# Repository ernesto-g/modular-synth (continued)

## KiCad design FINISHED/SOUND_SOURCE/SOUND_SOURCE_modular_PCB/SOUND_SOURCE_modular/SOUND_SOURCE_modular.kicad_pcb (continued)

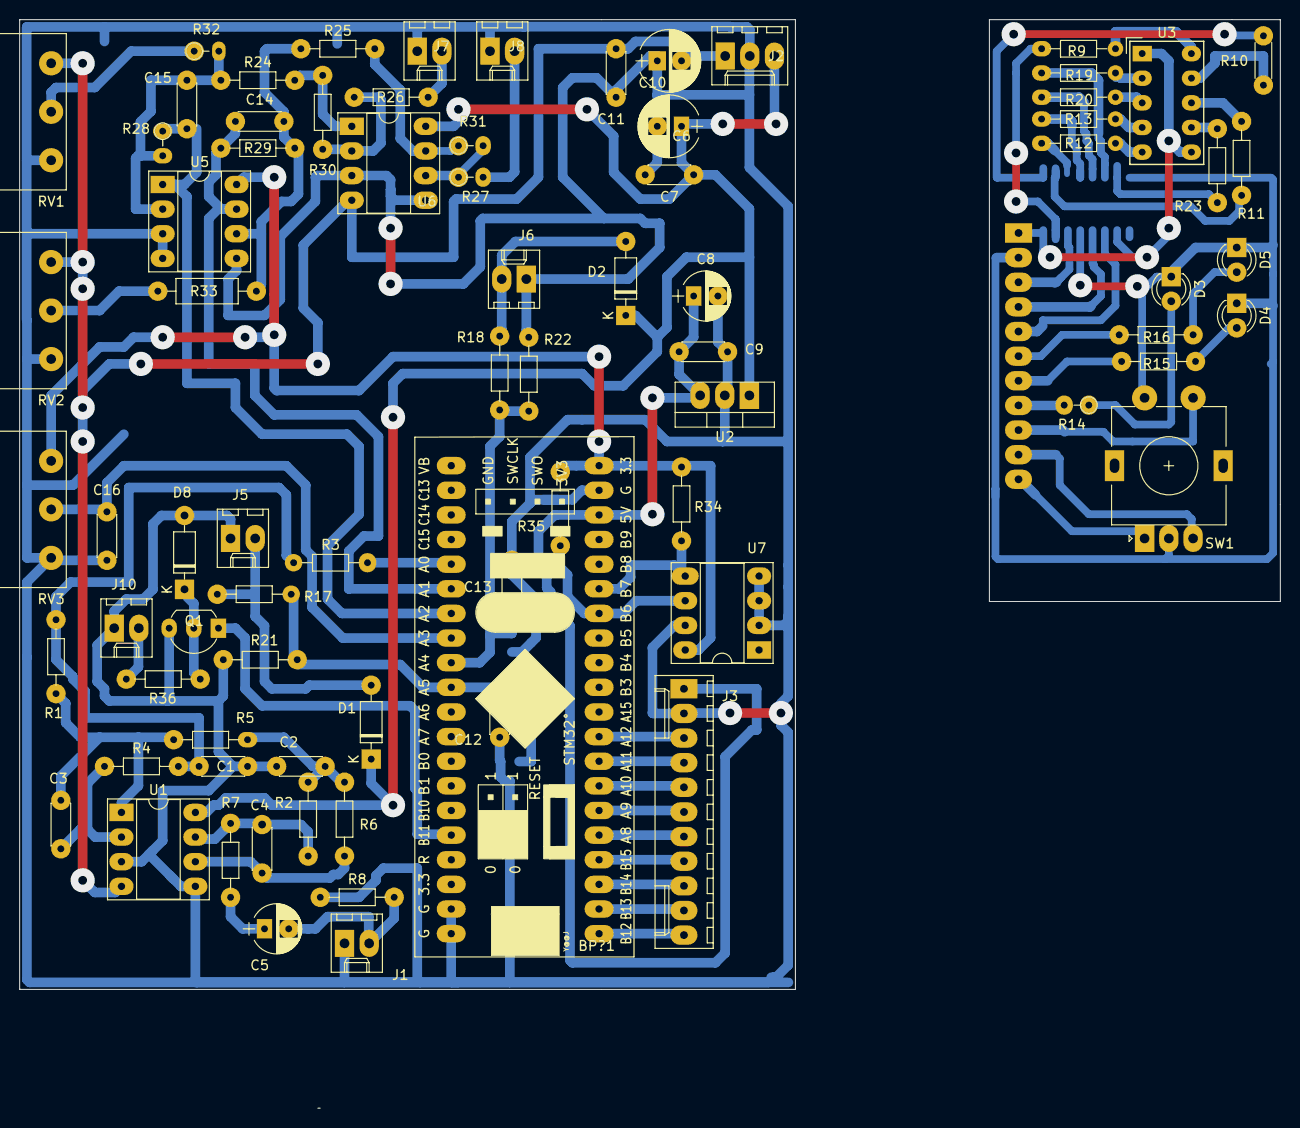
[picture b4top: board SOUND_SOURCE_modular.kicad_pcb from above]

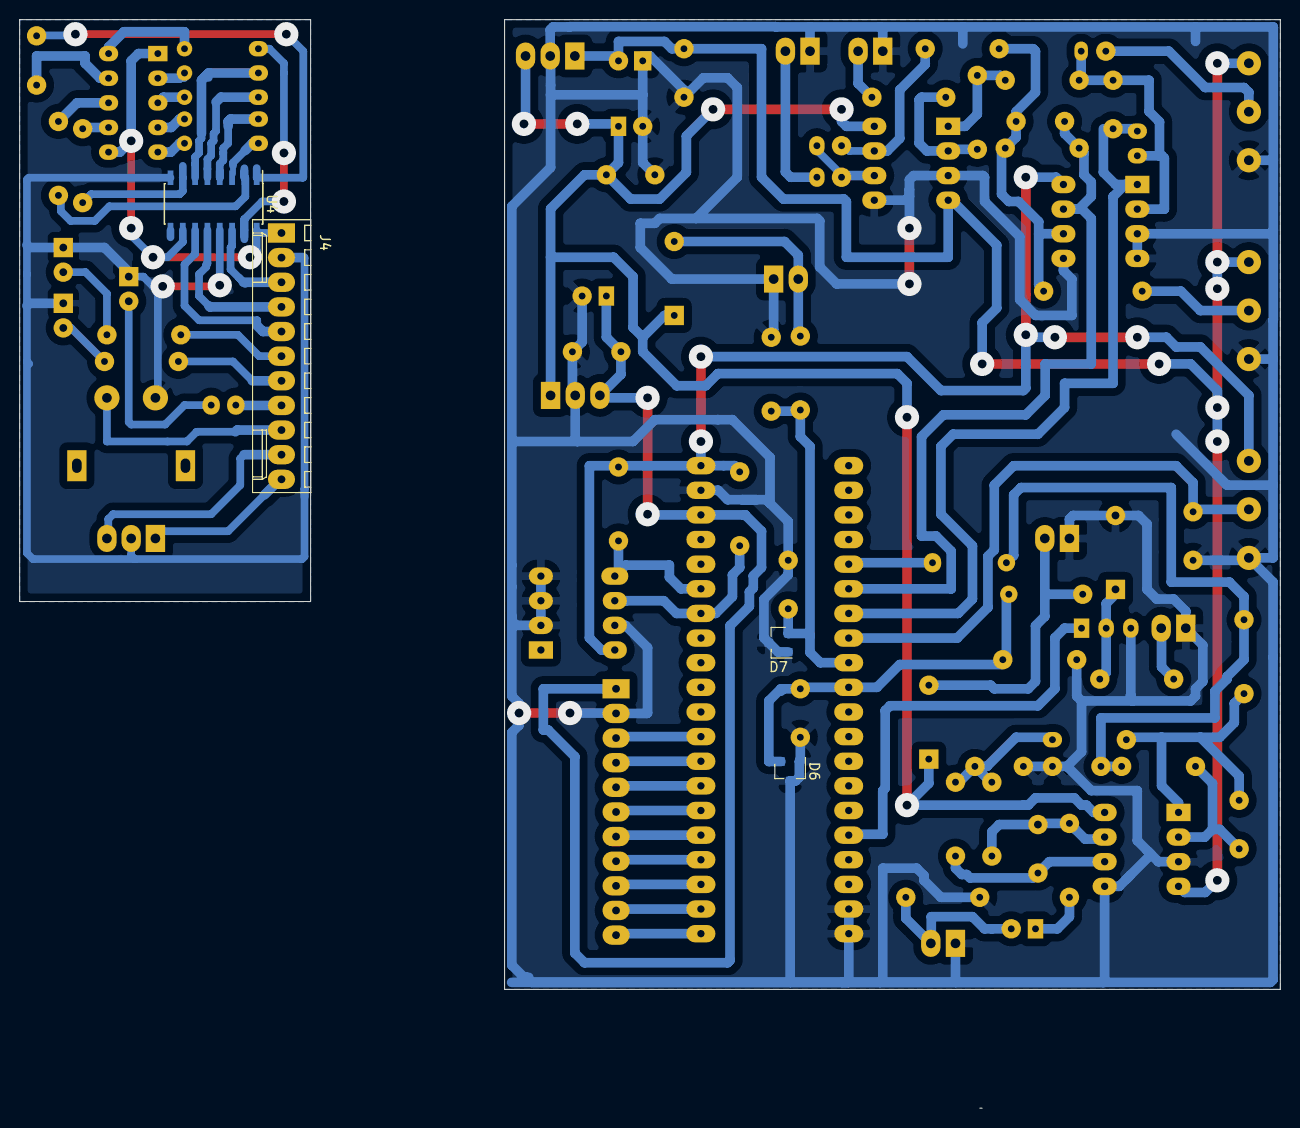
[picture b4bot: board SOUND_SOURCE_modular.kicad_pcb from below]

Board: 2 copper layers, 130.0 x 112.2 mm, 82 parts (4 on the bottom side), 75 nets.

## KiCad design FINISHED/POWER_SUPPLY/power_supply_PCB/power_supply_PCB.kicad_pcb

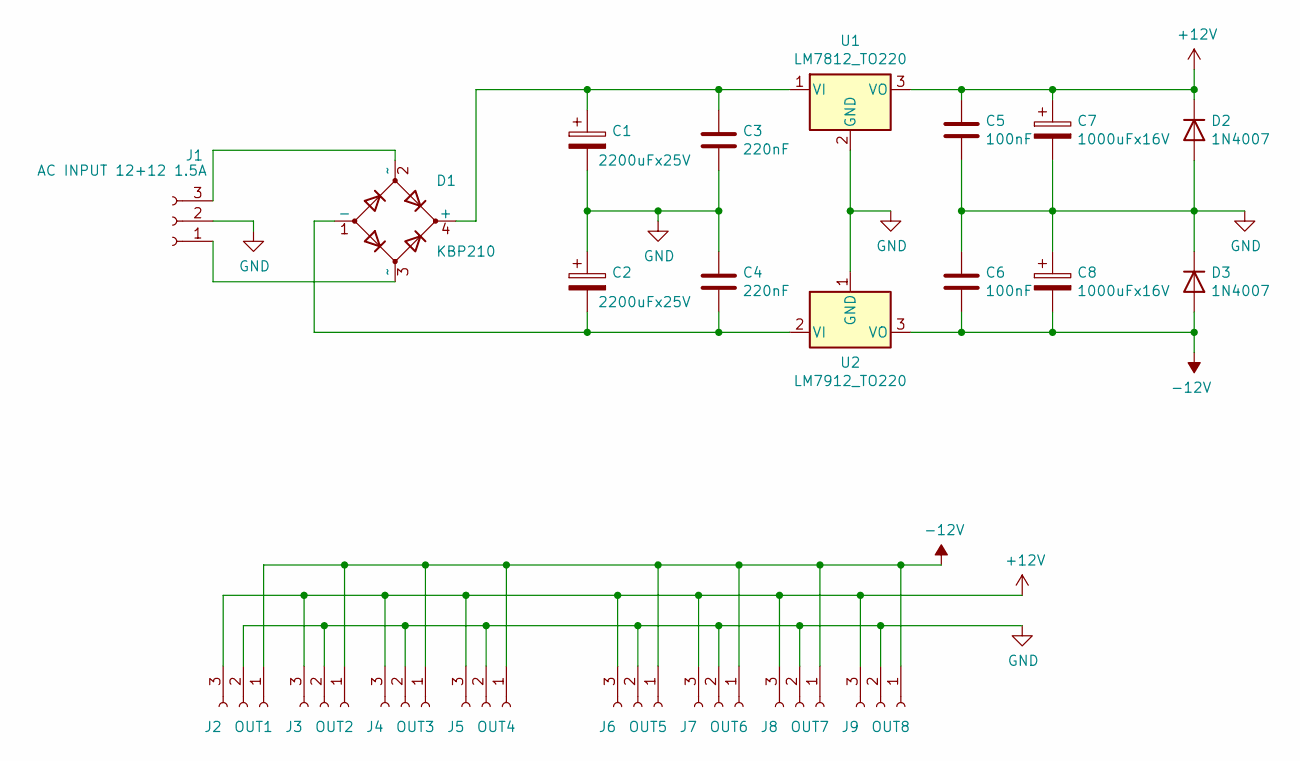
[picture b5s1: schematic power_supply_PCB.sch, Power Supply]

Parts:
C1, C2: 2200uFx25V; CP_Radial_D13.0mm_P5.00mm
C3, C4: 220nF; C_Disc_D11.0mm_W5.0mm_P7.50mm
C5, C6: 100nF; C_Disc_D5.0mm_W2.5mm_P5.00mm
C7, C8: 1000uFx16V; CP_Radial_D8.0mm_P3.50mm
D1: KBP210; Diode_Bridge_Vishay_KBU
D2, D3: 1N4007; D_DO-41_SOD81_P10.16mm_Horizontal
J1: AC INPUT 12+12 1.5A; TerminalBlock_Altech_AK300-3_P5.00mm
J2: OUT1; Molex_KK-6410-03_03x2.54mm_Straight
J3: OUT2; Molex_KK-6410-03_03x2.54mm_Straight
J4: OUT3; Molex_KK-6410-03_03x2.54mm_Straight
J5: OUT4; Molex_KK-6410-03_03x2.54mm_Straight
J6: OUT5; Molex_KK-6410-03_03x2.54mm_Straight
J7: OUT6; Molex_KK-6410-03_03x2.54mm_Straight
J8: OUT7; Molex_KK-6410-03_03x2.54mm_Straight
J9: OUT8; Molex_KK-6410-03_03x2.54mm_Straight
U1: LM7812_TO220; TO-220-3_Vertical
U2: LM7912_TO220; TO-220-3_Vertical

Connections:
+12V: C5.1, C7.1, D2.1 (K), J2.3, J3.3, J4.3, J5.3, J6.3, J7.3, J8.3, J9.3, U1.3 (VO)
-12V: C6.2, C8.2, D3.2 (A), J2.1, J3.1, J4.1, J5.1, J6.1, J7.1, J8.1, J9.1, U2.3 (VO)
GND: C1.2, C2.1, C3.2, C4.1, C5.2, C6.1, C7.2, C8.1, D2.2 (A), D3.1 (K), J1.2, J2.2, J3.2, J4.2, J5.2, J6.2, J7.2, J8.2, J9.2, U1.2 (GND), U2.1 (GND)
unnamed: C1.1, C3.1, D1.4 (+), U1.1 (VI)
unnamed: C2.2, C4.2, D1.1 (-), U2.2 (VI)
unnamed: D1.2 (~~), J1.3
unnamed: D1.3 (~~), J1.1

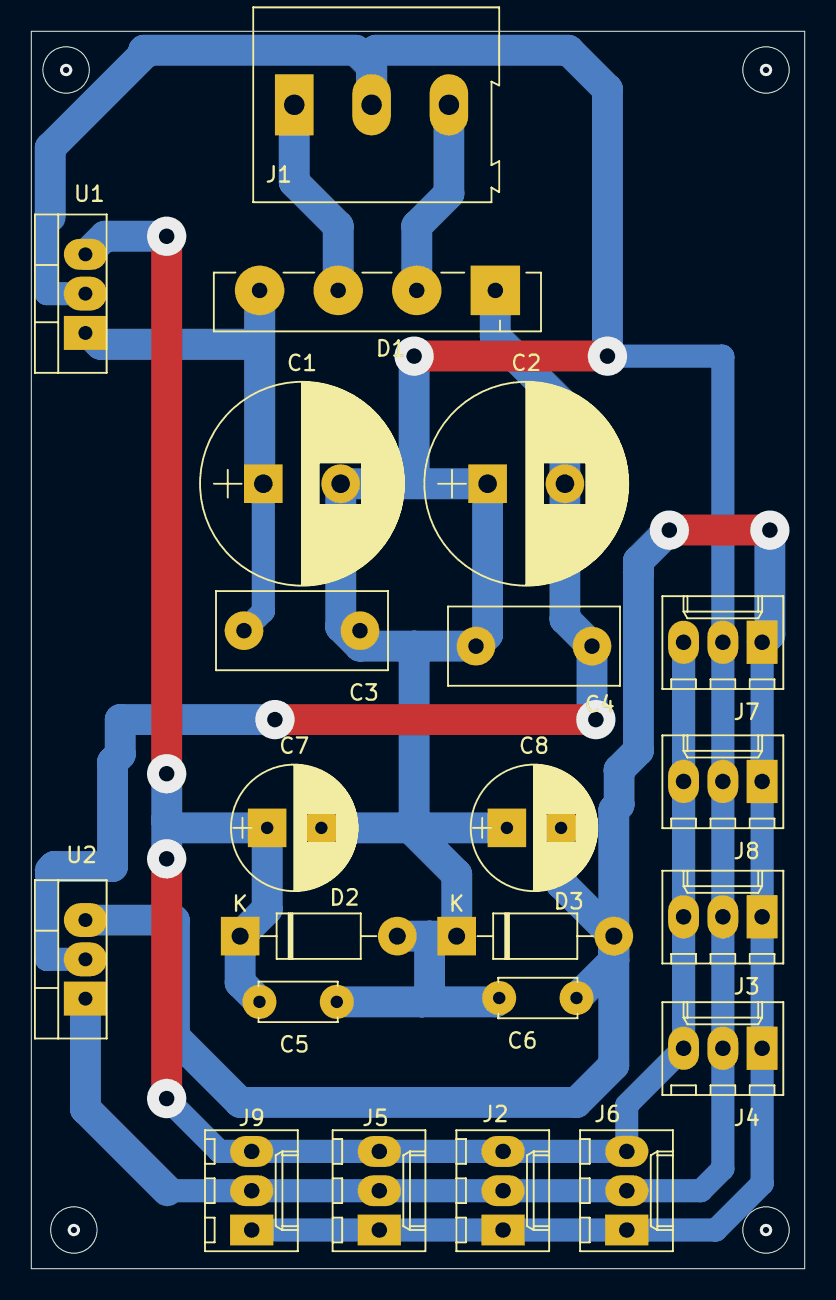
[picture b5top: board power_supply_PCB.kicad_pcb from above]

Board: 2 copper layers, 50.0 x 80.0 mm, 22 parts (0 on the bottom side), 7 nets.

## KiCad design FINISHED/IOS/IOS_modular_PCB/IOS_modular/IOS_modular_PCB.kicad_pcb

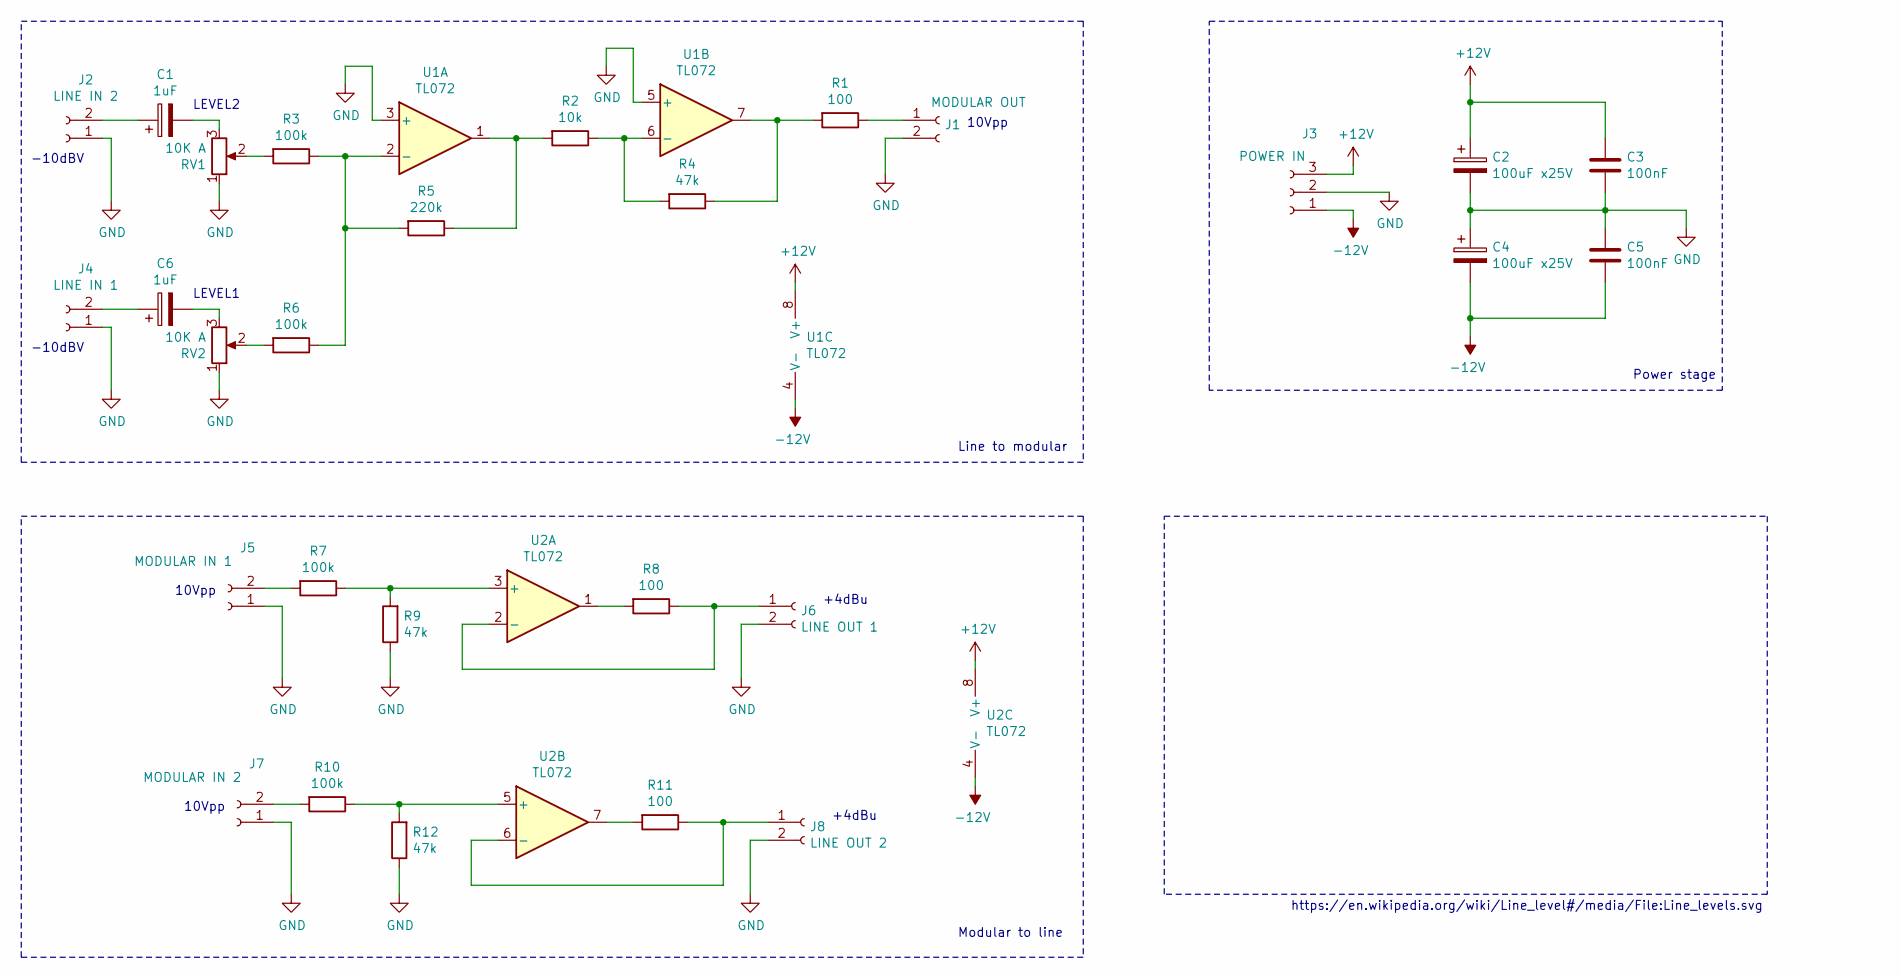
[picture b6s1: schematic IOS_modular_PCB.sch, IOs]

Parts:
C1, C6: 1uF; CP_Radial_D4.0mm_P2.00mm
C2, C4: 100uF x25V; CP_Radial_D6.3mm_P2.50mm
C3, C5: 100nF; C_Disc_D4.3mm_W1.9mm_P5.00mm
J1: MODULAR OUT; Molex_KK-6410-02_02x2.54mm_Straight
J2: LINE IN 2; Molex_KK-6410-02_02x2.54mm_Straight
J3: POWER IN; Molex_KK-6410-03_03x2.54mm_Straight
J4: LINE IN 1; Molex_KK-6410-02_02x2.54mm_Straight
J5: MODULAR IN 1; Molex_KK-6410-02_02x2.54mm_Straight
J6: LINE OUT 1; Molex_KK-6410-02_02x2.54mm_Straight
J7: MODULAR IN 2; Molex_KK-6410-02_02x2.54mm_Straight
J8: LINE OUT 2; Molex_KK-6410-02_02x2.54mm_Straight
R1, R8, R11: 100; R_Axial_DIN0204_L3.6mm_D1.6mm_P7.62mm_Horizontal
R2: 10k; R_Axial_DIN0204_L3.6mm_D1.6mm_P7.62mm_Horizontal
R3, R6, R7, R10: 100k; R_Axial_DIN0204_L3.6mm_D1.6mm_P7.62mm_Horizontal
R4, R9, R12: 47k; R_Axial_DIN0204_L3.6mm_D1.6mm_P7.62mm_Horizontal
R5: 220k; R_Axial_DIN0204_L3.6mm_D1.6mm_P7.62mm_Horizontal
RV1, RV2: 10K A; Potentiometer_Piher_PC-16_Single_Vertical
U1, U2: TL072; DIP-8_W7.62mm_Socket_LongPads

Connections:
+12V: C2.1, C3.1, J3.3, U1.8 (V+), U2.8 (V+)
-12V: C4.2, C5.2, J3.1, U1.4 (V-), U2.4 (V-)
GND: C2.2, C3.2, C4.1, C5.1, J1.2, J2.1, J3.2, J4.1, J5.1, J6.2, J7.1, J8.2, R9.1, R12.1, RV1.1, RV2.1, U1.3 (+), U1.5 (+)
unnamed: C1.1, J2.2
unnamed: C1.2, RV1.3
unnamed: C6.1, J4.2
unnamed: C6.2, RV2.3
unnamed: J1.1, R1.1
unnamed: J5.2, R7.2
unnamed: J6.1, R8.1, U2.2 (-)
unnamed: J7.2, R10.2
unnamed: J8.1, R11.1, U2.6 (-)
unnamed: R1.2, R4.1, U1.7
unnamed: R2.1, R4.2, U1.6 (-)
unnamed: R2.2, R5.1, U1.1
unnamed: R3.1, R5.2, R6.1, U1.2 (-)
unnamed: R3.2, RV1.2
unnamed: R6.2, RV2.2
unnamed: R7.1, R9.2, U2.3 (+)
unnamed: R8.2, U2.1
unnamed: R10.1, R12.2, U2.5 (+)
unnamed: R11.2, U2.7

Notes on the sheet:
LEVEL2
LEVEL1
Line to modular
Modular to line
Power stage
10Vpp
+4dBu
https://en.wikipedia.org/wiki/Line_level#/media/File:Line_levels.svg
-10dBV

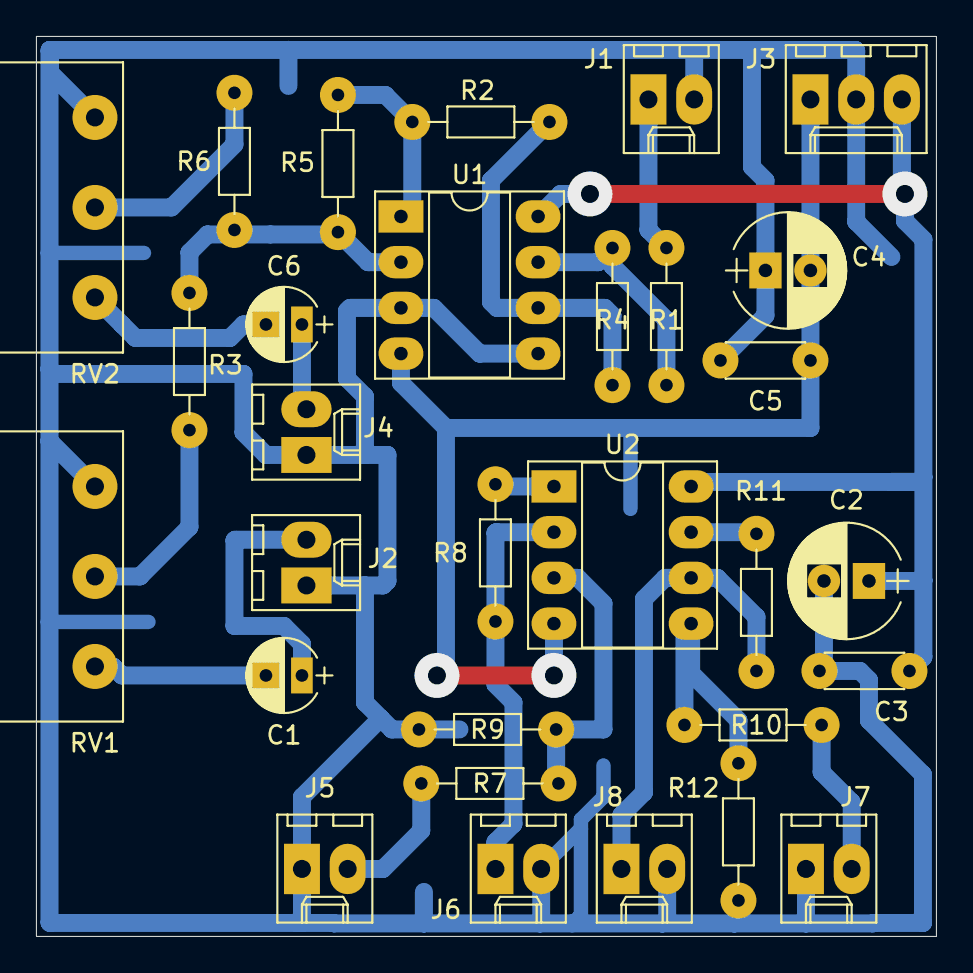
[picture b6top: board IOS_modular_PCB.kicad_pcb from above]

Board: 2 copper layers, 50.0 x 50.0 mm, 30 parts (0 on the bottom side), 22 nets.

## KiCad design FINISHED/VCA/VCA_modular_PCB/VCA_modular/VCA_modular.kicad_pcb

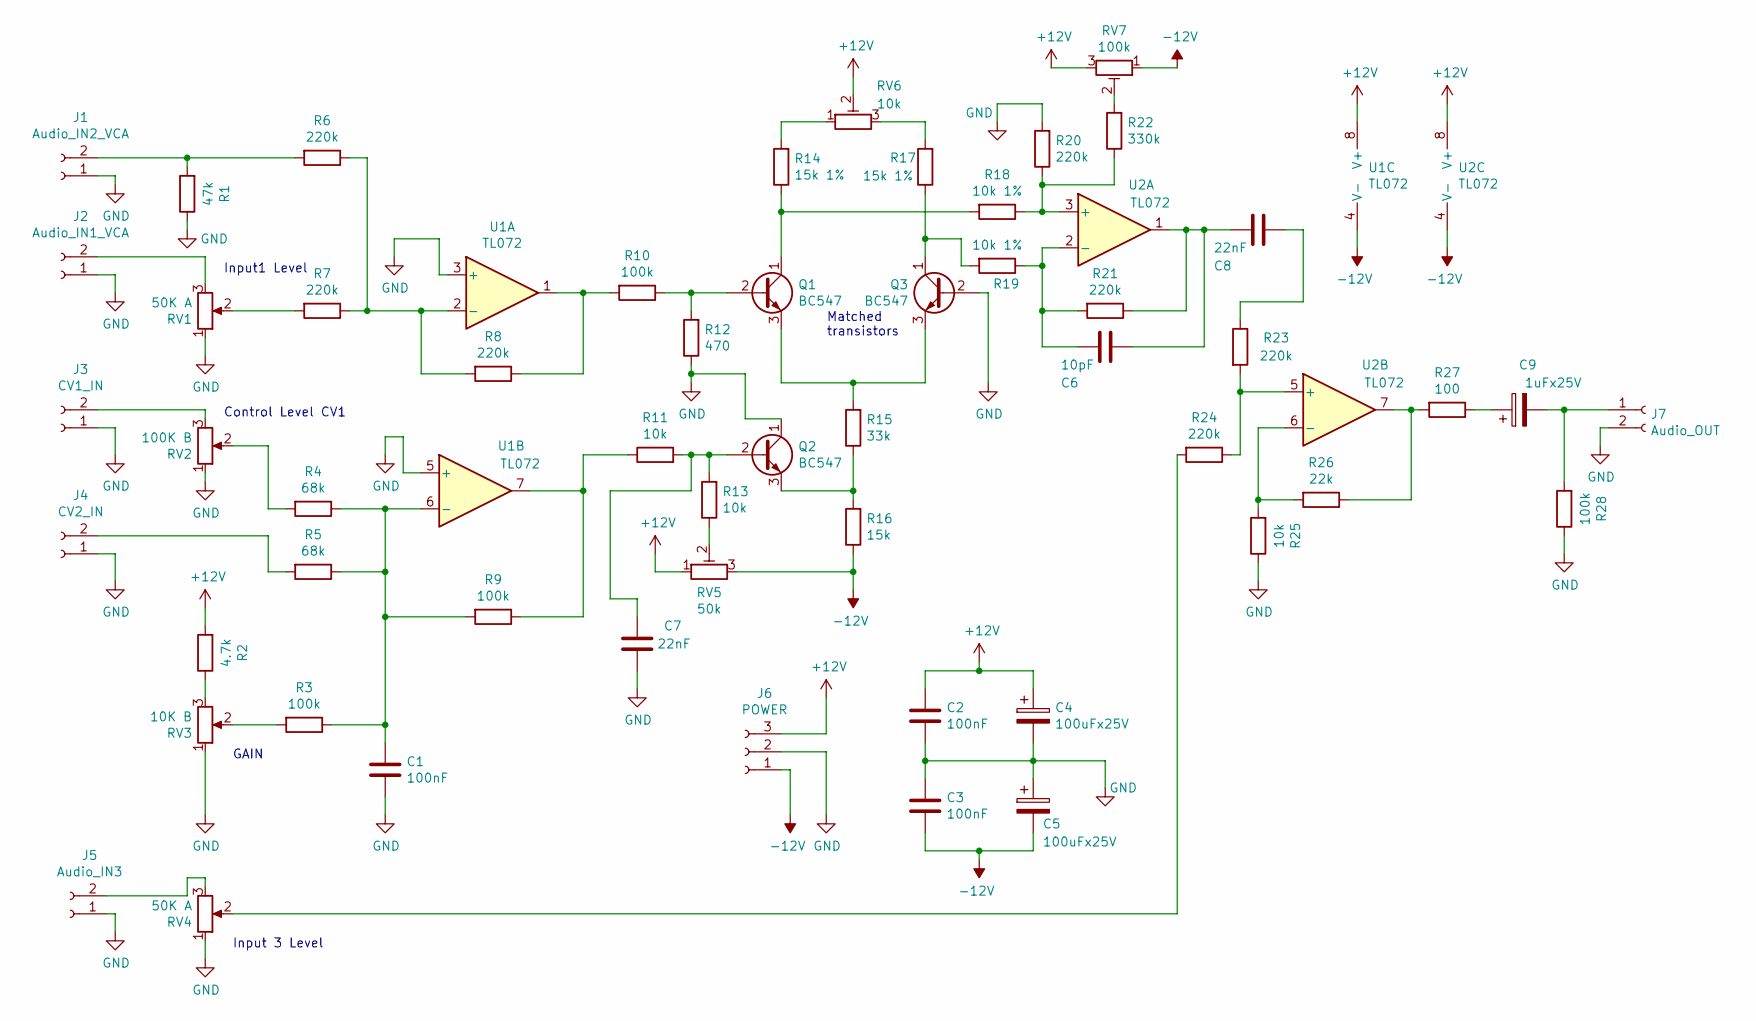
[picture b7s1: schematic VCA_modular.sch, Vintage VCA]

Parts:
C1, C2, C3: 100nF; C_Disc_D4.3mm_W1.9mm_P5.00mm
C4, C5: 100uFx25V; CP_Radial_D6.3mm_P2.50mm
C6: 10pF; C_Disc_D4.3mm_W1.9mm_P5.00mm
C7, C8: 22nF; C_Disc_D4.3mm_W1.9mm_P5.00mm
C9: 1uFx25V; CP_Radial_D6.3mm_P2.50mm
J1: Audio_IN2_VCA; Molex_KK-6410-02_02x2.54mm_Straight
J2: Audio_IN1_VCA; Molex_KK-6410-02_02x2.54mm_Straight
J3: CV1_IN; Molex_KK-6410-02_02x2.54mm_Straight
J4: CV2_IN; Molex_KK-6410-02_02x2.54mm_Straight
J5: Audio_IN3; Molex_KK-6410-02_02x2.54mm_Straight
J6: POWER; Molex_KK-6410-03_03x2.54mm_Straight
J7: Audio_OUT; Molex_KK-6410-02_02x2.54mm_Straight
Q1, Q2, Q3: BC547; TO-92_Inline
R1: 47k; R_Axial_DIN0204_L3.6mm_D1.6mm_P7.62mm_Horizontal
R2: 4.7k; R_Axial_DIN0204_L3.6mm_D1.6mm_P7.62mm_Horizontal
R3, R9, R10, R28: 100k; R_Axial_DIN0204_L3.6mm_D1.6mm_P7.62mm_Horizontal
R4, R5: 68k; R_Axial_DIN0204_L3.6mm_D1.6mm_P7.62mm_Horizontal
R6, R7, R8, R20, R21, R23, R24: 220k; R_Axial_DIN0204_L3.6mm_D1.6mm_P7.62mm_Horizontal
R11, R13, R25: 10k; R_Axial_DIN0204_L3.6mm_D1.6mm_P7.62mm_Horizontal
R12: 470; R_Axial_DIN0204_L3.6mm_D1.6mm_P7.62mm_Horizontal
R14, R17: 15k 1%; R_Axial_DIN0204_L3.6mm_D1.6mm_P7.62mm_Horizontal
R15: 33k; R_Axial_DIN0204_L3.6mm_D1.6mm_P7.62mm_Horizontal
R16: 15k; R_Axial_DIN0204_L3.6mm_D1.6mm_P7.62mm_Horizontal
R18, R19: 10k 1%; R_Axial_DIN0204_L3.6mm_D1.6mm_P7.62mm_Horizontal
R22: 330k; R_Axial_DIN0204_L3.6mm_D1.6mm_P7.62mm_Horizontal
R26: 22k; R_Axial_DIN0204_L3.6mm_D1.6mm_P7.62mm_Horizontal
R27: 100; R_Axial_DIN0204_L3.6mm_D1.6mm_P7.62mm_Horizontal
RV1, RV4: 50K A; Potentiometer_Piher_PC-16_Single_Vertical
RV2: 100K B; Potentiometer_Piher_PC-16_Single_Vertical
RV3: 10K B; Potentiometer_Piher_PC-16_Single_Vertical
RV5: 50k; Potentiometer_Trimmer_ACP_CA6v_Horizontal
RV6: 10k; Potentiometer_Trimmer_ACP_CA6v_Horizontal
RV7: 100k; Potentiometer_Trimmer_ACP_CA6v_Horizontal
U1, U2: TL072; DIP-8_W7.62mm_LongPads

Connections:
+12V: C2.1, C4.1, J6.3, R2.2, RV5.1, RV6.2, RV7.3, U1.8 (V+), U2.8 (V+)
-12V: C3.2, C5.2, J6.1, R16.1, RV5.3, RV7.1, U1.4 (V-), U2.4 (V-)
GND: C1.2, C2.2, C3.1, C4.2, C5.1, C7.1, J1.1, J2.1, J3.1, J4.1, J5.1, J6.2, J7.2, Q2.1 (C), Q3.2 (B), R1.1, R12.1, R20.2, R25.1, R28.1, RV1.1, RV2.1, RV3.1, RV4.1, U1.3 (+), U1.5 (+)
unnamed: C1.1, R3.1, R4.1, R5.1, R9.2, U1.6 (-)
unnamed: C6.1, C8.2, R21.1, U2.1
unnamed: C6.2, R19.1, R21.2, U2.2 (-)
unnamed: C7.2, Q2.2 (B), R11.2, R13.2
unnamed: C8.1, R23.1
unnamed: C9.1, R27.1
unnamed: C9.2, J7.1, R28.2
unnamed: J1.2, R1.2, R6.2
unnamed: J2.2, RV1.3
unnamed: J3.2, RV2.3
unnamed: J4.2, R5.2
unnamed: J5.2, RV4.3
unnamed: Q1.1 (C), R14.1, R18.2
unnamed: Q1.2 (B), R10.1, R12.2
unnamed: Q1.3 (E), Q3.3 (E), R15.2
unnamed: Q2.3 (E), R15.1, R16.2
unnamed: Q3.1 (C), R17.1, R19.2
unnamed: R2.1, RV3.3
unnamed: R3.2, RV3.2
unnamed: R4.2, RV2.2
unnamed: R6.1, R7.1, R8.2, U1.2 (-)
unnamed: R7.2, RV1.2
unnamed: R8.1, R10.2, U1.1
unnamed: R9.1, R11.1, U1.7
unnamed: R13.1, RV5.2
unnamed: R14.2, RV6.1
unnamed: R17.2, RV6.3
unnamed: R18.1, R20.1, R22.1, U2.3 (+)
unnamed: R22.2, RV7.2
unnamed: R23.2, R24.1, U2.5 (+)
unnamed: R24.2, RV4.2
unnamed: R25.2, R26.2, U2.6 (-)
unnamed: R26.1, R27.2, U2.7

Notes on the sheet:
Input1 Level
Control Level CV1
GAIN
Matched transistors
Input 3 Level

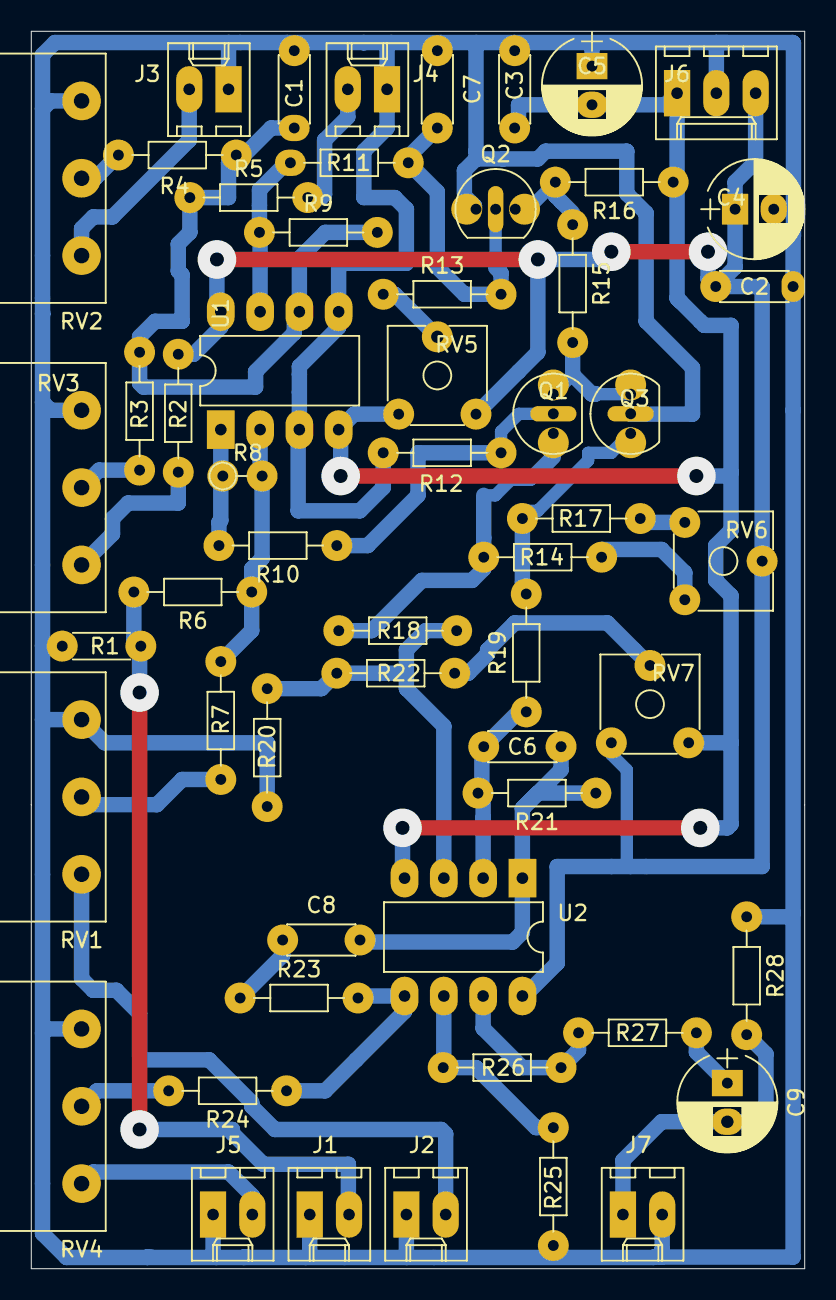
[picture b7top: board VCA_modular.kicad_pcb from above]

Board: 2 copper layers, 50.0 x 80.0 mm, 56 parts (0 on the bottom side), 36 nets.

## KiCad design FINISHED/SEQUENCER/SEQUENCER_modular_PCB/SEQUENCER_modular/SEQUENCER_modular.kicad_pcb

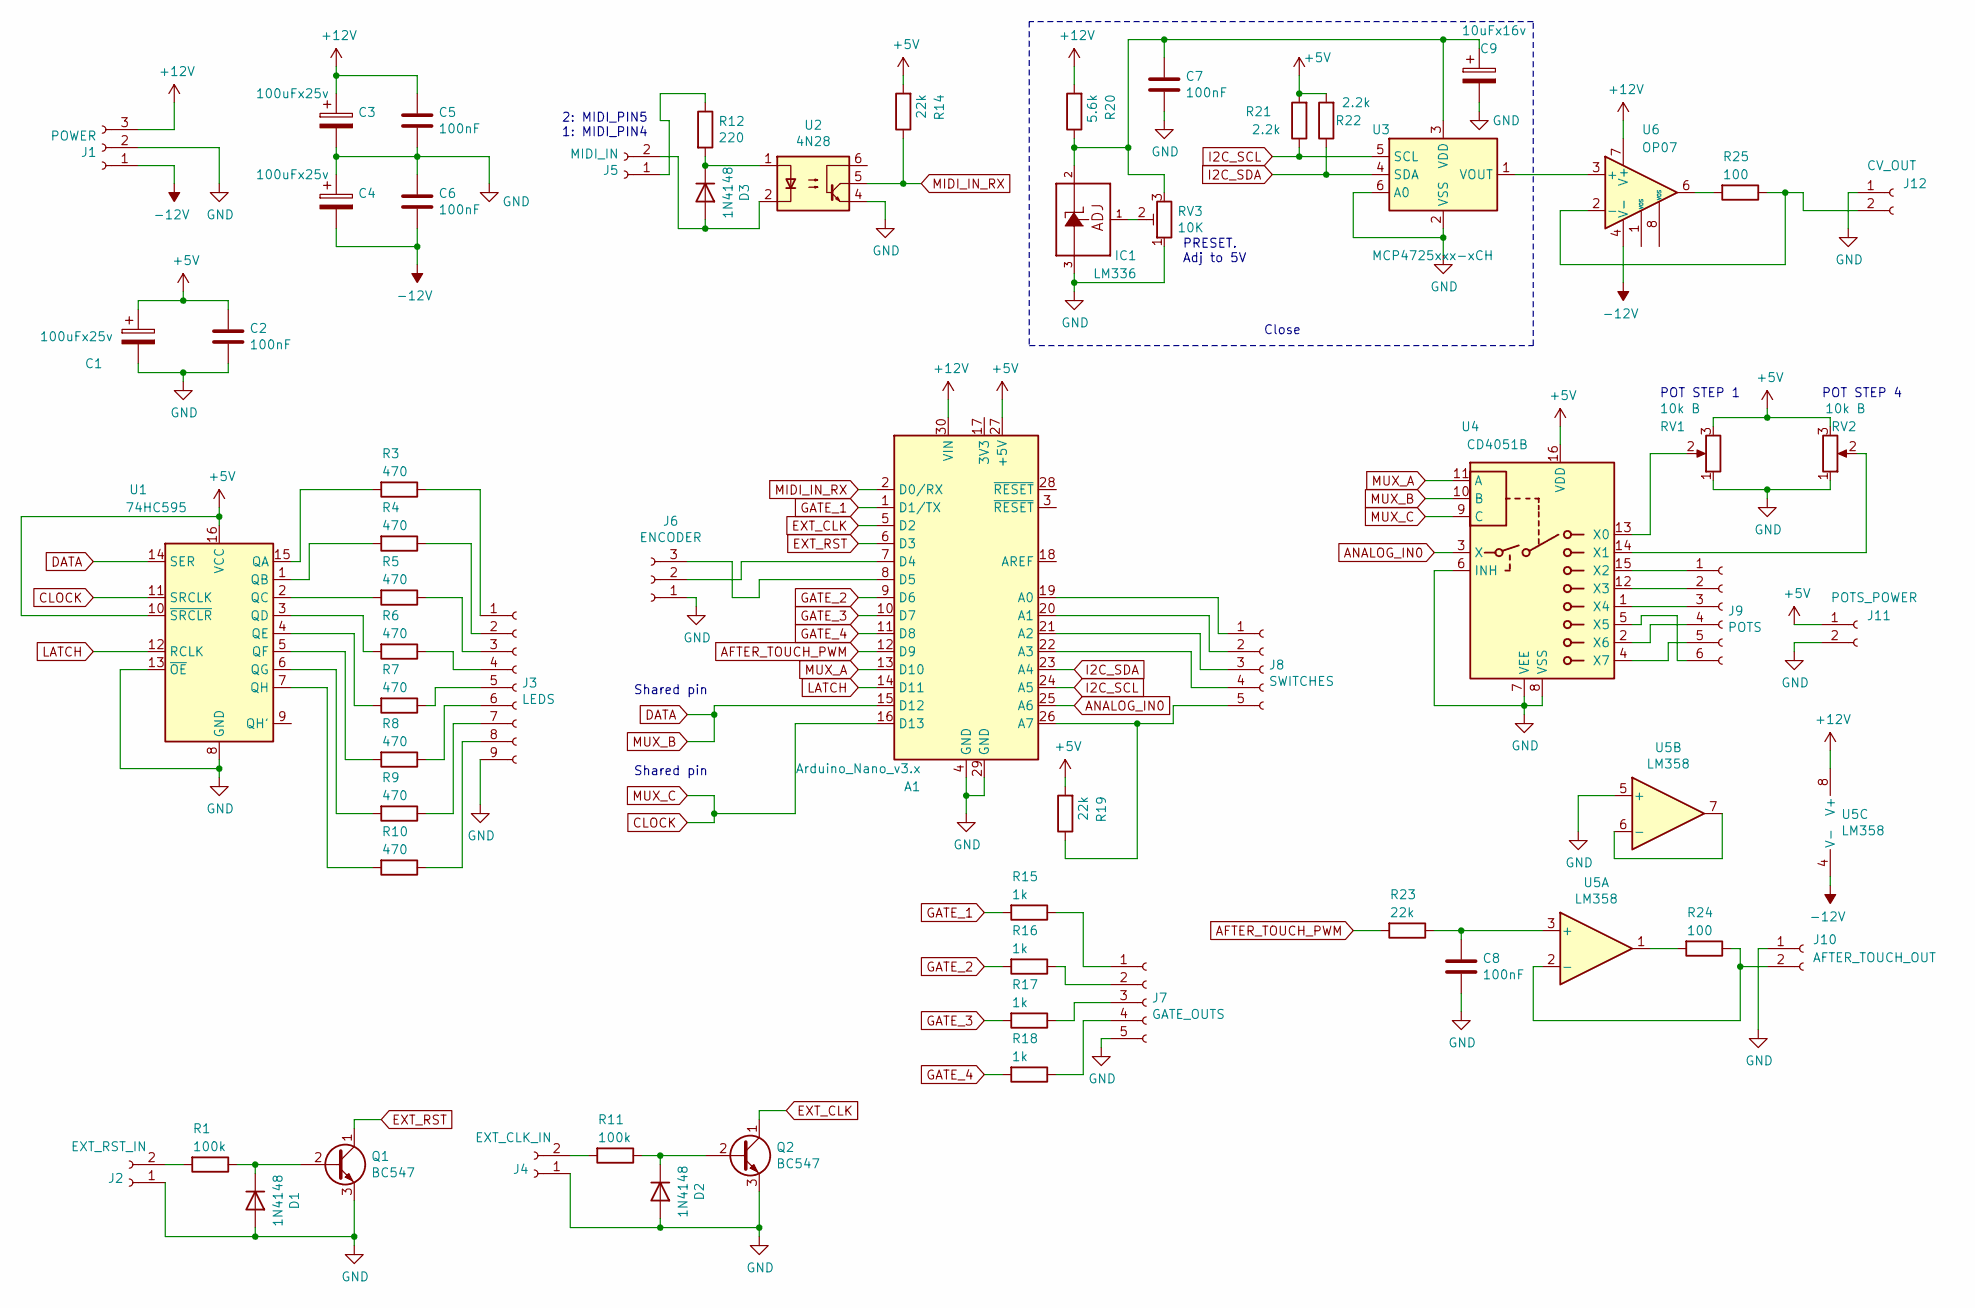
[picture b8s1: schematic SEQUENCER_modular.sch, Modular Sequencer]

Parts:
A1: Arduino_Nano_v3.x; Arduino_Nano
C1, C3, C4: 100uFx25v; CP_Radial_D5.0mm_P2.50mm
C2, C5, C6, C7, C8: 100nF; C_Disc_D5.1mm_W3.2mm_P5.00mm
C9: 10uFx16v; CP_Radial_D5.0mm_P2.50mm
D1, D2, D3: 1N4148; D_DO-35_SOD27_P7.62mm_Horizontal
IC1: LM336; TO-92_HandSolder
J1: POWER; Molex_KK-41791-03_03x3.96mm_Straight
J2: EXT_RST_IN; Molex_KK-41791-02_02x3.96mm_Straight
J3: LEDS; Molex_KK-6410-09_09x2.54mm_Straight
J4: EXT_CLK_IN; Molex_KK-41791-02_02x3.96mm_Straight
J5: MIDI_IN; Molex_KK-41791-02_02x3.96mm_Straight
J6: ENCODER; Molex_KK-41791-03_03x3.96mm_Straight
J7: GATE_OUTS; Molex_KK-6410-05_05x2.54mm_Straight
J8: SWITCHES; Molex_KK-6410-05_05x2.54mm_Straight
J9: POTS; Molex_KK-6410-06_06x2.54mm_Straight
J10: AFTER_TOUCH_OUT; Molex_KK-41791-02_02x3.96mm_Straight
J11: POTS_POWER; Molex_KK-41791-02_02x3.96mm_Straight
J12: CV_OUT; Molex_KK-41791-02_02x3.96mm_Straight
Q1, Q2: BC547; TO-92_HandSolder
R1, R11: 100k; R_Axial_DIN0204_L3.6mm_D1.6mm_P7.62mm_Horizontal
R3, R4, R5, R6, R7, R8, R9, R10: 470; R_Axial_DIN0204_L3.6mm_D1.6mm_P7.62mm_Horizontal
R12: 220; R_Axial_DIN0204_L3.6mm_D1.6mm_P7.62mm_Horizontal
R14, R19, R23: 22k; R_Axial_DIN0204_L3.6mm_D1.6mm_P7.62mm_Horizontal
R15, R16, R17, R18: 1k; R_Axial_DIN0204_L3.6mm_D1.6mm_P7.62mm_Horizontal
R20: 5.6k; R_Axial_DIN0204_L3.6mm_D1.6mm_P7.62mm_Horizontal
R21, R22: 2.2k; R_Axial_DIN0204_L3.6mm_D1.6mm_P7.62mm_Horizontal
R24, R25: 100; R_Axial_DIN0204_L3.6mm_D1.6mm_P7.62mm_Horizontal
RV1, RV2: 10k B; Potentiometer_Piher_PC-16_Single_Vertical
RV3: 10K; Potentiometer_Trimmer_ACP_CA6v_Horizontal
U1: 74HC595; DIP-16_W7.62mm_LongPads
U2: 4N28; DIP-6_W7.62mm
U3: MCP4725xxx-xCH; SOT-23-6
U4: CD4051B; DIP-16_W7.62mm_LongPads
U5: LM358; DIP-8_W7.62mm_LongPads
U6: OP07; DIP-8_W7.62mm_LongPads

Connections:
+5V: A1.27 (+5V), C1.1, C2.1, J11.1, R14.2, R19.2, R21.2, R22.2, RV1.3, RV2.3, U1.10 (~SRCLR), U1.16 (VCC), U4.16 (VDD)
+12V: A1.30 (VIN), C3.1, C5.1, J1.3, R20.2, U5.8 (V+), U6.7 (V+)
-12V: C4.2, C6.2, J1.1, U5.4 (V-), U6.4 (V-)
AFTER_TOUCH_PWM: A1.12 (D9), R23.2
ANALOG_IN0: A1.25 (A6), U4.3 (X)
CLOCK: A1.16 (D13), U1.11 (SRCLK), U4.9 (C)
DATA: A1.15 (D12), U1.14 (SER), U4.10 (B)
EXT_CLK: A1.5 (D2), Q2.1 (C)
EXT_RST: A1.6 (D3), Q1.1 (C)
GATE_1: A1.1 (D1/TX), R15.2
GATE_2: A1.9 (D6), R16.2
GATE_3: A1.10 (D7), R17.2
GATE_4: A1.11 (D8), R18.2
GND: A1.4 (GND), A1.29 (GND), C1.2, C2.2, C3.2, C4.1, C5.2, C6.1, C7.2, C8.2, C9.2, D1.2 (A), D2.2 (A), IC1.3 (A), J1.2, J2.1, J3.9, J4.1, J6.1, J7.5, J10.1, J11.2, J12.1, Q1.3 (E), Q2.3 (E), RV1.1, RV2.1, RV3.1, U1.8 (GND), U1.13 (~OE), U2.4, U3.2 (VSS), U3.6 (A0), U4.6 (INH), U4.7 (VEE), U4.8 (VSS), U5.5 (+)
I2C_SCL: A1.24 (A5), R21.1, U3.5 (SCL)
I2C_SDA: A1.23 (A4), R22.1, U3.4 (SDA)
LATCH: A1.14 (D11), U1.12 (RCLK)
MIDI_IN_RX: A1.2 (D0/RX), R14.1, U2.5
MUX_A: A1.13 (D10), U4.11 (A)
unnamed: A1.7 (D4), J6.2
unnamed: A1.8 (D5), J6.3
unnamed: A1.19 (A0), J8.1
unnamed: A1.20 (A1), J8.2
unnamed: A1.21 (A2), J8.3
unnamed: A1.22 (A3), J8.4
unnamed: A1.26 (A7), J8.5, R19.1
unnamed: C7.1, C9.1, IC1.2 (C), R20.1, RV3.3, U3.3 (VDD)
unnamed: C8.1, R23.1, U5.3 (+)
unnamed: D1.1 (K), Q1.2 (B), R1.1
unnamed: D2.1 (K), Q2.2 (B), R11.1
unnamed: D3.1 (K), R12.2, U2.1
unnamed: D3.2 (A), J5.2, U2.2
unnamed: IC1.1 (ADJ), RV3.2
unnamed: J2.2, R1.2
unnamed: J3.1, R3.1
unnamed: J3.2, R4.1
unnamed: J3.3, R5.1
unnamed: J3.4, R6.1
unnamed: J3.5, R7.1
unnamed: J3.6, R8.1
unnamed: J3.7, R9.1
unnamed: J3.8, R10.1
unnamed: J4.2, R11.2
unnamed: J5.1, R12.1
unnamed: J7.1, R15.1
unnamed: J7.2, R16.1
unnamed: J7.3, R17.1
unnamed: J7.4, R18.1
unnamed: J9.1, U4.15 (X2)
unnamed: J9.2, U4.12 (X3)
unnamed: J9.3, U4.1 (X4)
unnamed: J9.4, U4.2 (X6)
unnamed: J9.5, U4.4 (X7)
unnamed: J9.6, U4.5 (X5)
unnamed: J10.2, R24.1, U5.2 (-)
unnamed: J12.2, R25.1, U6.2 (-)
unnamed: R3.2, U1.15 (QA)
unnamed: R4.2, U1.1 (QB)
unnamed: R5.2, U1.2 (QC)
unnamed: R6.2, U1.3 (QD)
unnamed: R7.2, U1.4 (QE)
unnamed: R8.2, U1.5 (QF)
unnamed: R9.2, U1.6 (QG)
unnamed: R10.2, U1.7 (QH)
unnamed: R24.2, U5.1
unnamed: R25.2, U6.6
unnamed: RV1.2, U4.13 (X0)
unnamed: RV2.2, U4.14 (X1)
unnamed: U3.1 (VOUT), U6.3 (+)
unnamed: U5.6 (-), U5.7

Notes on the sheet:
2: MIDI_PIN5 1: MIDI_PIN4
Shared pin
POT STEP 1
POT STEP 4
Close
PRESET. Adj to 5V

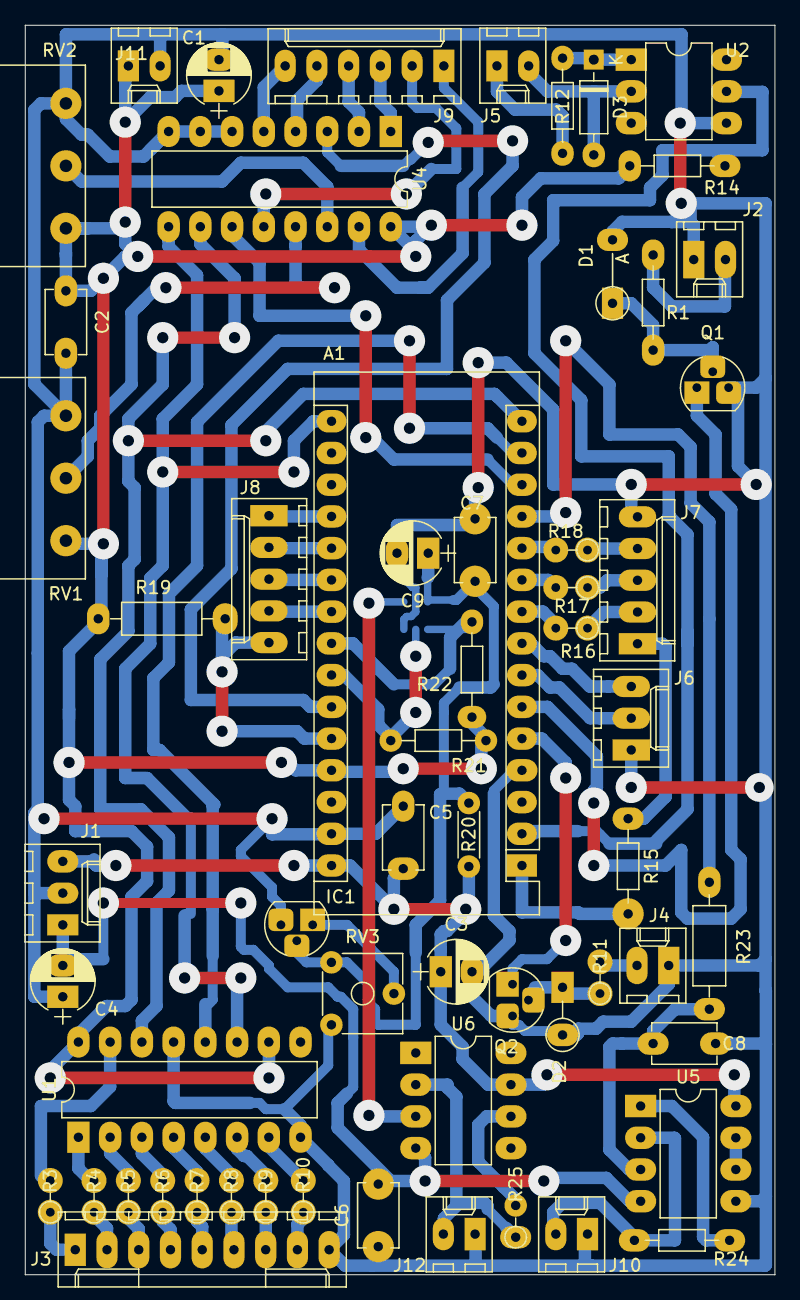
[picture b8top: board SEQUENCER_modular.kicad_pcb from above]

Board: 2 copper layers, 60.0 x 100.0 mm, 60 parts (1 on the bottom side), 70 nets.

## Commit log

2020-06-21 encoder and tempo. Direction button
2020-06-21 direction feature finished
2020-06-21 gates timeouts working
2020-06-22 probability feature for gates
2020-06-23 leds indications
2020-06-25 MIDI support. incomplete
2020-06-26 gate control in midi manager
2020-06-26 clock divisor button OK
2020-06-27 external clock src. Config struct
2020-06-28 reset in implementation
2020-06-28 config modes with long press OK
2020-07-01 gate repetitions
2020-07-02 repeat gates mode finished
2020-07-03 arpeggiator OK
2020-07-05 eeprom management. save basic configuration
2020-07-05 tempo in eeprom
2020-07-05 euclidean mode without offset
2020-07-07 offset for euclidean mode
2020-07-08 license included in all files
2020-07-18 fix switches NO mode
2020-08-01 first commit with all modules information
2020-08-01 readme changes
2020-08-01 external data removed
2020-08-09 power supply schematic OK
2020-08-09 gate trigger does not happen when knob is set to zero in track 0
2020-08-09 fix in sequencer firmware. reset event bug in pendulum mode
2020-08-09 Power supply moved to finished. Name fixing for diy files
2020-08-15 trees module added
2020-08-15 sound source firmware project included. first commit
2020-08-15 adc included.
2020-08-15 gate input support
2020-09-06 Display class working
2020-09-08 Ui class and encoder
2020-09-09 Configuration menu OK
2020-09-10 fix scales in sequencer. sound source: calibration state machine OK
2020-09-12 gitignore file added
2020-09-12 sound source eeprom management
2020-09-12 sound source shape modulation
2020-09-13 sound source: fine tune scale and indication. change oscillator update display timings changed
2020-09-13 sound source: 4 new sounds implemented.
2020-09-13 sound source licence in files
2020-09-13 sound source: config led at start
2020-09-13 Sound source added to finished projects
2020-09-14 Sound source manual
2020-09-16 sound source autotrigger fix
2020-09-16 sound source async memory write for oscillator selection
2020-09-16 sound source manual fix. pictures and readme
2020-09-16 sound source pic on readme
2020-09-17 sound source pdf manual
2020-09-17 sound source fix autotrigger threshold level
2020-09-17 sound source circuit fix cv anf fm inputs. increase capacitor
2020-09-23 lfo first commit
2020-09-24 lfo wavetables ok
2020-09-24 lfo encoder management and leds indications. free and phase mode OK
2020-09-25 lfo ios hal. Sequencer mode incomplete
2020-09-25 LFO. BoC output
2020-09-25 LFO. set steps with pots
2020-09-25 LFO OK finished.
2020-09-25 LFO project structure updated
2020-09-26 lfo clk in sync
2020-09-26 lfox3 manual
2020-09-26 readme updated
2020-10-03 sound source fix min octave to C2
2020-10-04 chord master module first commit. Based on sound source
2020-10-07 chord master. quality and variation params test
2020-10-07 chord master: class chord manager
2020-10-07 chord manager: voicing parameter working
2020-10-10 chord master: hysteresis for quality, voicings and variation inputs
2020-10-10 chord manager: harmonizer
2020-10-18 atenuverter and mixer project added
2020-10-19 sequencer: new feature: set root note for scale
2020-10-19 sequencer manual update
2020-10-20 sequencer root note saved in eeprom
2020-11-13 LFOx3 fix mode switch with 3 modes
2020-11-14 ATV and mixer OK
2020-11-15 simple sequencer project finished
2020-11-16 images updated
2021-05-30 cambio en UI de sound source y chord master
2021-05-30 VCF project
2021-05-30 readme updated with VCF.
